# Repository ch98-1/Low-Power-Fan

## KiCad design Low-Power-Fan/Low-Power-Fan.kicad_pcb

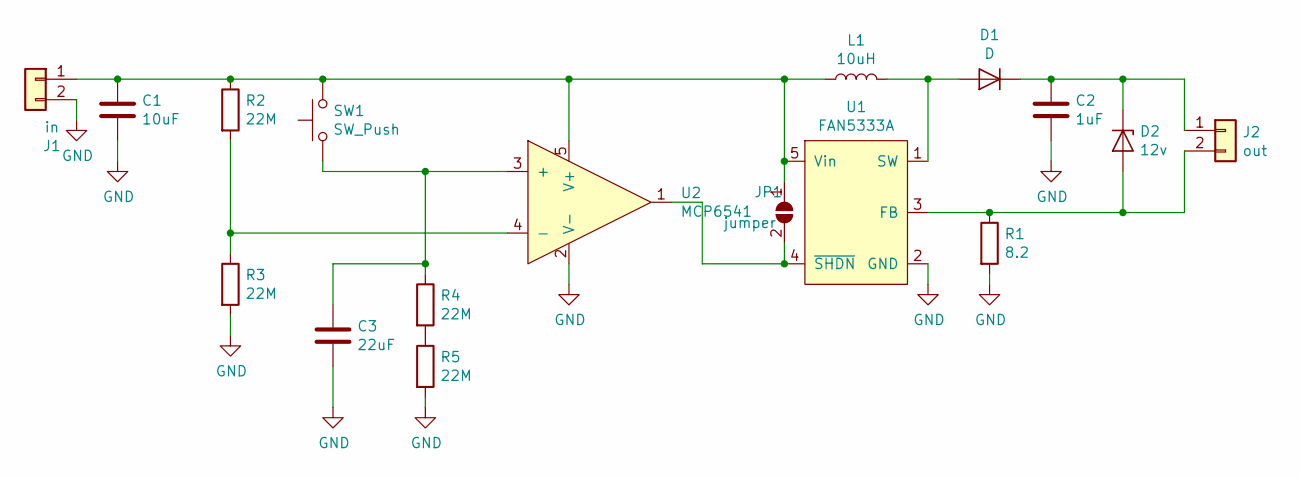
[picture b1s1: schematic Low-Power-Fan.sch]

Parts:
C1: 10uF; C_0603_1608Metric
C2: 1uF; C_0603_1608Metric
C3: 22uF; C_0805_2012Metric
D1: D; D_SOT-23_ANK
D2: 12v; D_SOT-23_ANK
J1: in; BatteryHolder_MPD_BC2AAPC_2xAA
J2: out; PinHeader_1x02_P2.54mm_Vertical
JP1: jumper; SolderJumper-2_P1.3mm_Open_Pad1.0x1.5mm
L1: 10uH; L_1812_4532Metric
R1: 8.2; R_0603_1608Metric
R2, R3, R4, R5: 22M; R_0603_1608Metric
SW1: SW_Push; SW_SPST_PTS645
U1: FAN5333A; SOT-23-5
U2: MCP6541; SOT-23-5

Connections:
GND: C1.2, C2.2, C3.2, J1.2, R1.2, R3.2, R5.2, U1.2 (GND), U2.2 (V-)
unnamed: C1.1, J1.1, JP1.1 (A), L1.1, R2.1, SW1.2, U1.5 (Vin), U2.5 (V+)
unnamed: C2.1, D1.1 (K), D2.1 (K), J2.1
unnamed: C3.1, R4.1, SW1.1, U2.3 (+)
unnamed: D1.2 (A), L1.2, U1.1 (SW)
unnamed: D2.2 (A), J2.2, R1.1, U1.3 (FB)
unnamed: JP1.2 (B), U1.4 (~SHDN), U2.1
unnamed: R2.2, R3.1, U2.4 (-)
unnamed: R4.2, R5.1

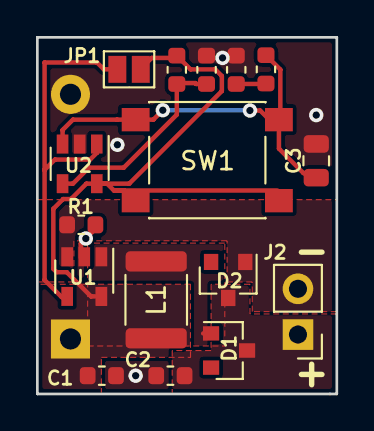
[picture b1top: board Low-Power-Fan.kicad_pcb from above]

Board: 2 copper layers, 16.6 x 19.8 mm, 17 parts (1 on the bottom side), 9 nets.

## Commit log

2019-01-20 Created Project Files
2019-01-20 Added initial BOM
2019-01-21 Updated BOM with better formatting
2019-01-21 Finished prototype design
2019-01-29 Added 10 minute timer and a switch. Updated resistor for higher current.
2019-01-30 changed solder mask clearence to make reflow easier
2019-02-07 Capacitor 3 replaced with correct size
2019-02-07 Connected one side of the capacitor to ground
2019-02-07 Revert "Connected one side of the capacitor to ground"
    This reverts commit a7569e6a569e54939577e6c551374c5e72ad59fc.
